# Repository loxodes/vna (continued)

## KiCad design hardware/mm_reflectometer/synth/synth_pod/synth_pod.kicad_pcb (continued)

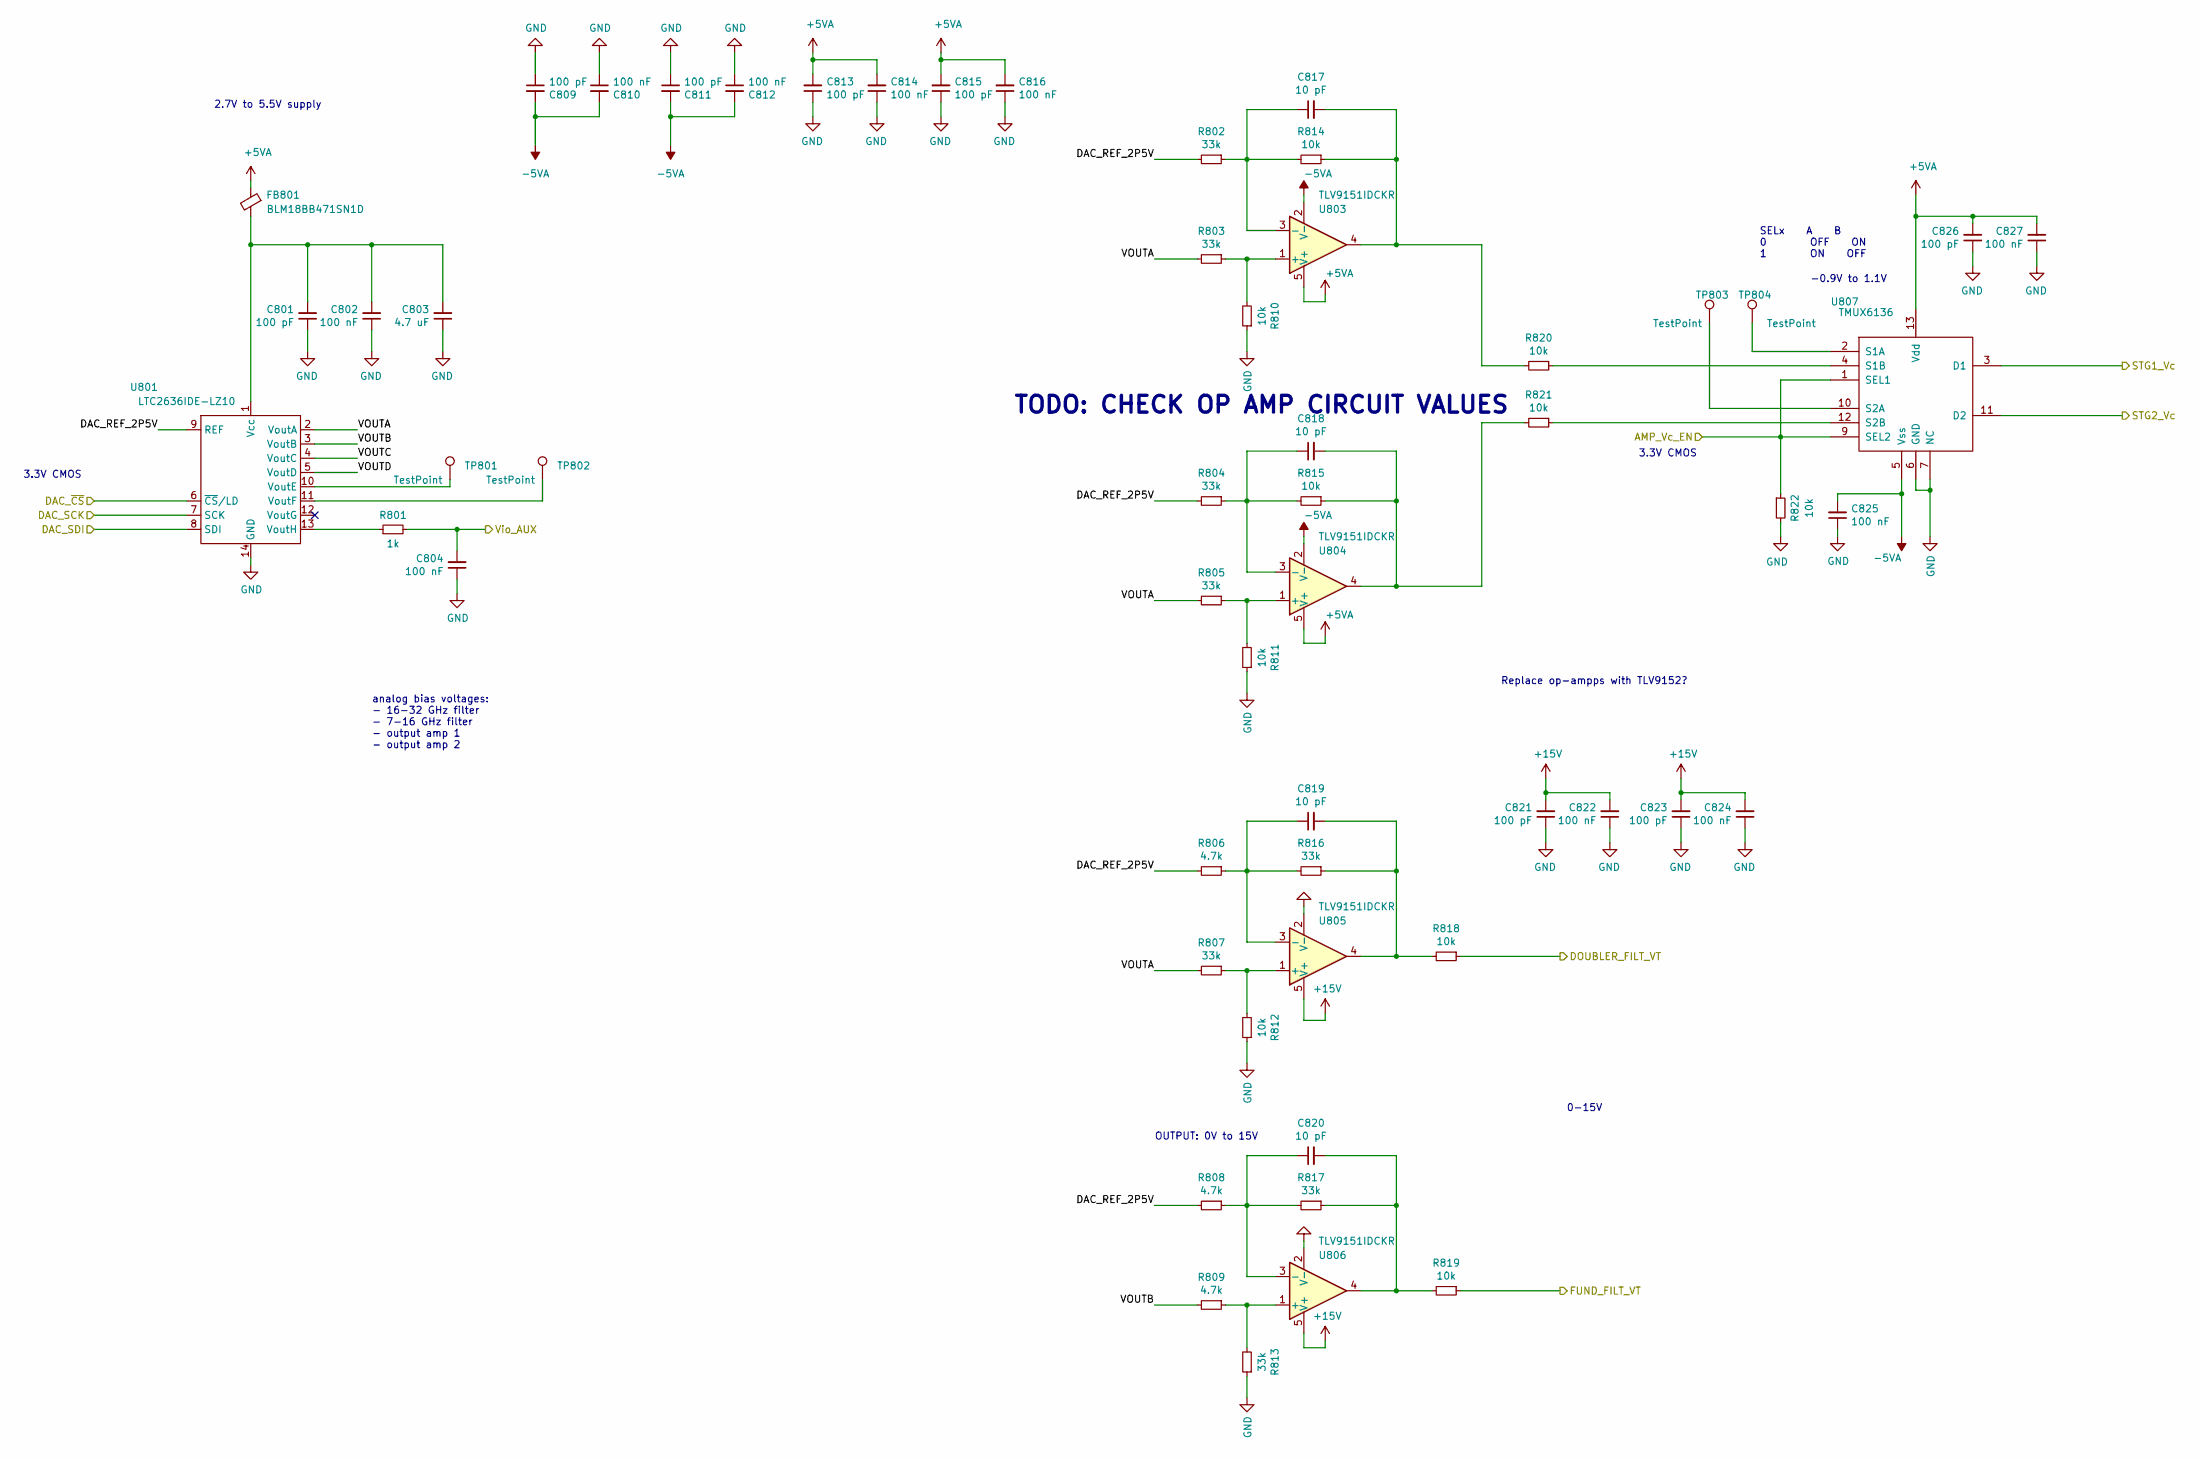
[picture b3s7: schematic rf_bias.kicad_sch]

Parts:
C801, C809, C811, C813, C815, C821, C823, C826: 100 pF; C_0402_1005Metric
C802, C804, C810, C812, C814, C816, C822, C824, C825, C827: 100 nF; C_0402_1005Metric
C803: 4.7 uF; C_0402_1005Metric
C817, C818, C819, C820: 10 pF; C_0402_1005Metric
FB801: BLM18BB471SN1D; L_0603_1608Metric
R801: 1k; R_0402_1005Metric
R802, R803, R804, R805, R807, R813, R816, R817: 33k; R_0402_1005Metric
R806, R808, R809: 4.7k; R_0402_1005Metric
R810, R811, R812, R814, R815, R818, R819, R820, R821, R822: 10k; R_0402_1005Metric
TP801, TP802, TP803, TP804: TestPoint; TestPoint_Pad_D1.5mm
U801: LTC2636IDE-LZ10; DFN-14-1EP_3x4mm_P0.5mm_EP1.7x3.3mm; mpn LTC2636-LZ10; digikey# LTC2636IDE-LZ10#PBF-ND
U803, U804, U805, U806: TLV9151IDCKR; SOT-353_SC-70-5
U807: TMUX6136; TSSOP-16_4.4x5mm_P0.65mm

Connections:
+5VA: C813.2, C814.2, C815.2, C816.2, C826.2, C827.2, FB801.1, U803.5 (V+), U804.5 (V+), U807.13 (Vdd); also elsewhere on the board
+15V: C821.2, C822.2, C823.2, C824.2, U805.5 (V+), U806.5 (V+); also elsewhere on the board
-5VA: C809.2, C810.2, C811.2, C812.2, C825.2, U803.2 (V-), U804.2 (V-), U807.5 (Vss); also elsewhere on the board
/AMP_Vc_EN: R822.1, U807.1 (SEL1), U807.9 (SEL2); also elsewhere on the board
/BIAS_DAC_SCK: U801.7 (SCK); also elsewhere on the board
/BIAS_DAC_SDI: U801.8 (SDI); also elsewhere on the board
/BIAS_DAC_~CS: U801.6 (~CS/LD); also elsewhere on the board
/DOUBLER_FILT_VT: R819.1; also elsewhere on the board
/FUND_FILT_VT: R818.1; also elsewhere on the board
/STG1_Vc: U807.3 (D1); also elsewhere on the board
/STG2_Vc: U807.11 (D2); also elsewhere on the board
/Vio_AUX: C804.2, R801.2
/rf_bias/DAC_REF_2P5V: R802.2, R804.2, R806.2, R808.2, U801.9 (REF)
/rf_bias/VOUTA: R803.2, R805.2, R807.2, U801.2 (VoutA)
/rf_bias/VOUTB: R809.2, U801.3 (VoutB)
/rf_bias/VOUTC: U801.4 (VoutC)
/rf_bias/VOUTD: U801.5 (VoutD)
GND: C801.1, C802.1, C803.1, C804.1, C809.1, C810.1, C811.1, C812.1, C813.1, C814.1, C815.1, C816.1, C821.1, C822.1, C823.1, C824.1, C825.1, C826.1, C827.1, R810.1, R811.1, R812.1, R813.1, R822.2, U801.14 (GND), U801.15 (EP), U805.2 (V-), U806.2 (V-), U807.6 (GND), U807.7 (NC), U807.8 (NC), U807.14 (NC), U807.15 (NC), U807.16 (NC); also elsewhere on the board
unnamed: C801.2, C802.2, C803.2, FB801.2, U801.1 (Vcc)
unnamed: C817.1, R802.1, R814.2, U803.3 (-)
unnamed: C817.2, R814.1, R820.2, U803.4
unnamed: C818.1, R804.1, R815.2, U804.3 (-)
unnamed: C818.2, R815.1, R821.2, U804.4
unnamed: C819.1, R806.1, R816.2, U805.3 (-)
unnamed: C819.2, R816.1, R818.2, U805.4
unnamed: C820.1, R808.1, R817.2, U806.3 (-)
unnamed: C820.2, R817.1, R819.2, U806.4
unnamed: R801.1, U801.13 (VoutH)
unnamed: R803.1, R810.2, U803.1 (+)
unnamed: R805.1, R811.2, U804.1 (+)
unnamed: R807.1, R812.2, U805.1 (+)
unnamed: R809.1, R813.2, U806.1 (+)
unnamed: R820.1, U807.4 (S1B)
unnamed: R821.1, U807.12 (S2B)
unnamed: TP801.1, U801.10 (VoutE)
unnamed: TP802.1, U801.11 (VoutF)
unnamed: TP803.1, U807.10 (S2A)
unnamed: TP804.1, U807.2 (S1A)

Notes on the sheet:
analog bias voltages: - 16-32 GHz filter - 7-16 GHz filter - output amp 1 - output amp 2
3.3V CMOS
TODO: CHECK OP AMP CIRCUIT VALUES
-0.9V to 1.1V
0-15V
2.7V to 5.5V supply
Replace op-ampps with TLV9152?
SELx A B 0 OFF ON 1 ON OFF
OUTPUT: 0V to 15V

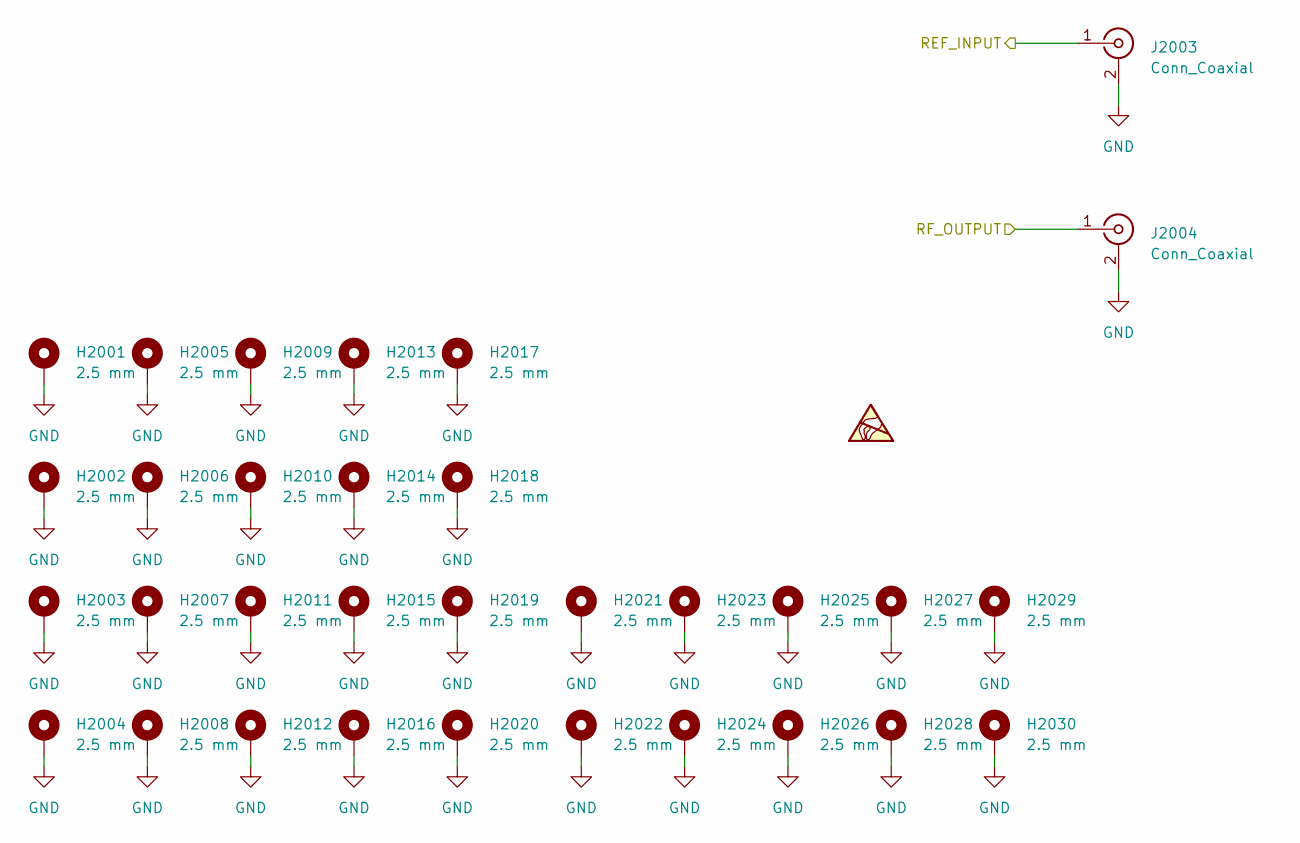
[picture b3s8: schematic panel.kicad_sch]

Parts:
H2001, H2002, H2003, H2004, H2005, H2006, H2007, H2008, H2009, H2010, H2011, H2012, H2013, H2014, H2015, H2016, H2017, H2018, H2019, H2020, H2021, H2022, H2023, H2024, H2025, H2026, H2027, H2028, H2029, H2030: 2.5 mm; MountingHole_2.5mm_Pad_Via
J2003: Conn_Coaxial; SMA_Cinch_142-0711-821_EdgeMount
J2004: Conn_Coaxial; sw_edge_oshpark_4layer

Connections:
/REF_IN: J2003.1 (In); also elsewhere on the board
/panel/RF_OUTPUT: J2004.1 (In); also elsewhere on the board
GND: H2001.1, H2002.1, H2003.1, H2004.1, H2005.1, H2006.1, H2007.1, H2008.1, H2009.1, H2010.1, H2011.1, H2012.1, H2013.1, H2014.1, H2015.1, H2016.1, H2017.1, H2018.1, H2019.1, H2020.1, H2021.1, H2022.1, H2023.1, H2024.1, H2025.1, H2026.1, H2027.1, H2028.1, H2029.1, H2030.1, J2003.2 (Ext), J2004.2 (Ext); also elsewhere on the board

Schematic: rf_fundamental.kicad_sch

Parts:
AT401: ATS2012; mpn ATS2012-xxdB-XX
C401, C405, C406, C409, C412: 10 nF; C_0402_1005Metric
C402, C407, C408, C413: 100 pF; C_0402_1005Metric
C403, C410, C411: 1 uF; C_0402_1005Metric
C404: C_Small; C_0402_1005Metric
FB401, FB402, FB403, FB404: BLM15GG471SZ1D; L_0402_1005Metric
R401, R402: R_Small; R_0402_1005Metric
U401: MAAM-011101; TDFN6; mpn MAAM-011101-TR1000; digikey# 1465-1283-1-ND
U402: ADMV8416; LFCSP-40-1EP_6x6mm_P0.5mm_EP4.7x4.7mm; mpn ADMV8416ACPZ; mouser# 584-ADMV8416ACPZ

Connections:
+3.3VA: FB401.1; also elsewhere on the board
+5VA: FB403.1; also elsewhere on the board
-5VA: FB404.1; also elsewhere on the board
/FUND_FILT_VCTL: R401.1
/FUND_FILT_VT: R402.1; also elsewhere on the board
/fundamental_b/FUND_B_IN: AT401.1; also elsewhere on the board
/fundamental_b/FUND_B_OUT: U402.26 (RFOUT); also elsewhere on the board
GND: AT401.3, C401.1, C402.1, C403.1, C405.1, C406.1, C407.1, C408.1, C409.1, C410.1, C411.1, C412.1, C413.1, U401.2 (NC), U401.4 (NC), U401.5 (NC), U401.6 (NC), U401.7 (EP), U402.1 (NC), U402.2 (NC), U402.3 (NC), U402.4 (GND), U402.6 (GND), U402.7 (NC), U402.8 (NC), U402.9 (NC), U402.10 (NC), U402.12 (GND), U402.14 (NC), U402.16 (GND), U402.17 (NC), U402.18 (GND), U402.20 (NC), U402.21 (NC), U402.22 (NC), U402.23 (NC), U402.24 (NC), U402.25 (GND), U402.27 (GND), U402.28 (NC), U402.29 (NC), U402.30 (NC), U402.31 (NC), U402.32 (NC), U402.33 (NC), U402.34 (NC), U402.35 (NC), U402.36 (NC), U402.37 (NC), U402.38 (NC), U402.39 (NC), U402.40 (NC), U402.41 (GND); also elsewhere on the board
unnamed: AT401.2, U401.3 (RFin)
unnamed: C401.2, R401.2, U402.15 (VCTL)
unnamed: C402.2, C405.2, R402.2, U402.19 (VTUNE)
unnamed: C403.2, C406.2, C408.2, FB401.2, FB402.1
unnamed: C404.1, FB402.2, U401.1 (RFout)
unnamed: C404.2, U402.5 (RFIN)
unnamed: C407.2, C409.2, C410.2, FB404.2, U402.11 (VEE)
unnamed: C411.2, C412.2, C413.2, FB403.2, U402.13 (VDD)

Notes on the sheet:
ADMV8416
0-15V ANALOG
3.3V CMOS
6.3-18 GHz

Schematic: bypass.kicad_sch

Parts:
C1001, C1002: 10 nF; C_0402_1005Metric
J1001, J1002: Conn_Coaxial; SF2921-61345
R1001, R1002: 50; R_0402_1005Metric

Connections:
/bypass/BYPASS_IN: C1002.2, R1002.1; also elsewhere on the board
/bypass/BYPASS_OUT: C1001.2, R1001.1; also elsewhere on the board
GND: J1001.2 (Ext), J1002.2 (Ext), R1001.2, R1002.2; also elsewhere on the board
unnamed: C1001.1, J1002.1 (In)
unnamed: C1002.1, J1001.1 (In)

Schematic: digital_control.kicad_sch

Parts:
J1401: SYZYGY-STD; SYZYGY_standard_pod

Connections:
+5VP: J1401.2 (+5V)
/AMP_Vc_EN: J1401.12 (S7_D3N); also elsewhere on the board
/ATT_CLK: J1401.28 (S23); also elsewhere on the board
/ATT_LE: J1401.26 (S21); also elsewhere on the board
/ATT_SERIN: J1401.30 (S25); also elsewhere on the board
/ATT_SEROUT: J1401.32 (S27); also elsewhere on the board
/BIAS_DAC_SCK: J1401.7 (S2_D0N); also elsewhere on the board
/BIAS_DAC_SDI: J1401.5 (S0_D0P); also elsewhere on the board
/BIAS_DAC_~CS: J1401.9 (S4_D2P); also elsewhere on the board
/CLK_N: J1401.36 (C2P_CLKN)
/CLK_P: J1401.34 (C2P_CLKP)
/OUT_SW_EN: J1401.20 (S15_D7N); also elsewhere on the board
/OUT_SW_V1: J1401.22 (S17); also elsewhere on the board
/OUT_SW_V2: J1401.24 (S19); also elsewhere on the board
/PLL_CE: J1401.11 (S6_D2N); also elsewhere on the board
/PLL_LD: J1401.19 (S14_D6N); also elsewhere on the board
/PLL_MUTE: J1401.18 (S13_D7P); also elsewhere on the board
/PLL_MUX: J1401.21 (S16); also elsewhere on the board
/PLL_SCK: J1401.13 (S8_D4P); also elsewhere on the board
/PLL_SDI: J1401.15 (S10_D4N); also elsewhere on the board
/PLL_SYNC: J1401.16 (S11_D5N); also elsewhere on the board
/PLL_~CS: J1401.17 (S12_D6P); also elsewhere on the board
/REFSW_SD2: J1401.14 (S9_D5P); also elsewhere on the board
/REF_EN: J1401.6 (S1_D1P); also elsewhere on the board
/REF_SEL: J1401.8 (S3_D1N); also elsewhere on the board
/RELAY_EN: J1401.10 (S5_D3P); also elsewhere on the board
/TLM_ADC_DIN: J1401.25 (S20); also elsewhere on the board
/TLM_ADC_DOUT: J1401.27 (S22); also elsewhere on the board
/TLM_ADC_SCLK: J1401.23 (S18); also elsewhere on the board
/TLM_ADC_~CS: J1401.29 (S24); also elsewhere on the board
/ctrl_power/~FPGA_RESET: J1401.31 (S26); also elsewhere on the board
/digital_control/R_GA: J1401.4 (R_GA); also elsewhere on the board
/digital_control/SCL: J1401.1 (SCL); also elsewhere on the board
/digital_control/SDA: J1401.3 (SDA); also elsewhere on the board
GND: J1401.41 (GND); also elsewhere on the board

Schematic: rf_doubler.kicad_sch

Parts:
AT501: ATS2012; mpn ATS2012-xxdB-XX
C501, C508, C515, C516: 1 uF; C_0402_1005Metric
C502, C504, C506, C510, C512, C514, C517: 10 nF; C_0402_1005Metric
C503, C507: 100 nF; C_0402_1005Metric
C505, C509, C511, C513, C518: 100 pF; C_0402_1005Metric
FB501, FB502, FB503, FB504: BLM15GG471SZ1D; L_0402_1005Metric
R501: 640; R_0402_1005Metric
R502: 4.7k; R_0402_1005Metric
R503, R504: R_Small; R_0402_1005Metric
U501: MAAM-011101; TDFN6; mpn MAAM-011101-TR1000; digikey# 1465-1283-1-ND
U502: XX1000-QT; QFN-16-1EP_3x3mm_P0.5mm_EP1.45x1.45mm; mpn XX1000-QT-0G0T
U503: ADMV8432; LFCSP-40-1EP_6x6mm_P0.5mm_EP4.7x4.7mm; mpn ADMV8432ACPZ; mouser# 584-ADMV8432ACPZ

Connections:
+3.3VA: FB501.1; also elsewhere on the board
+5VA: FB503.1; also elsewhere on the board
-5VA: C507.1, C509.1, FB504.1, R502.1, U502.6 (Vss); also elsewhere on the board
/DOUBLER_FILT_VCTL: R503.1
/DOUBLER_FILT_VT: R504.1; also elsewhere on the board
/highband/HIGHBAND_IN: AT501.1; also elsewhere on the board
/highband/HIGHBAND_OUT: U503.26 (RFOUT); also elsewhere on the board
/highband/Vg2: U502.7 (Vg2); also elsewhere on the board
/highband/active_bias/Vd: U502.13 (Vd2); also elsewhere on the board
/highband/active_bias/Vp: C506.2, C508.2, U502.15 (Vd1); also elsewhere on the board
GND: AT501.3, C501.1, C502.1, C503.2, C505.2, C506.1, C507.2, C508.1, C509.2, C510.1, C511.1, C512.1, C513.1, C514.1, C515.1, C516.1, C517.1, C518.1, R501.2, U501.2 (NC), U501.4 (NC), U501.5 (NC), U501.6 (NC), U501.7 (EP), U502.1 (NC), U502.2 (GND), U502.4 (GND), U502.8 (NC), U502.9 (GND), U502.11 (GND), U502.12 (NC), U502.14 (NC), U502.16 (NC), U502.17 (GND), U503.1 (NC), U503.2 (NC), U503.3 (NC), U503.4 (GND), U503.6 (GND), U503.7 (NC), U503.8 (NC), U503.9 (NC), U503.10 (NC), U503.12 (GND), U503.14 (NC), U503.16 (GND), U503.17 (NC), U503.18 (GND), U503.20 (NC), U503.21 (NC), U503.22 (NC), U503.23 (NC), U503.24 (NC), U503.25 (GND), U503.27 (GND), U503.28 (NC), U503.29 (NC), U503.30 (NC), U503.31 (NC), U503.32 (NC), U503.33 (NC), U503.34 (NC), U503.35 (NC), U503.36 (NC), U503.37 (NC), U503.38 (NC), U503.39 (NC), U503.40 (NC), U503.41 (GND); also elsewhere on the board
unnamed: AT501.2, U501.3 (RFin)
unnamed: C501.2, C502.2, FB501.2, FB502.1
unnamed: C503.1, C505.1, R501.1, R502.2, U502.5 (Vg1)
unnamed: C504.1, FB502.2, U501.1 (RFout)
unnamed: C504.2, U502.3 (RFin)
unnamed: C510.2, R503.2, U503.15 (VCTL)
unnamed: C511.2, C512.2, R504.2, U503.19 (VTUNE)
unnamed: C513.2, C514.2, C515.2, FB504.2, U503.11 (VEE)
unnamed: C516.2, C517.2, C518.2, FB503.2, U503.13 (VDD)
unnamed: U502.10 (RFout), U503.5 (RFIN)

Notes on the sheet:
TODO: VERIFY FOOTPRINT
3.3V CMOS
0-15V ANALOG
Sequence: GND, +5V, -5V, VCTL

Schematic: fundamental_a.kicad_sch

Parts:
C901, C904, C905: 10 nF; C_0402_1005Metric
C902, C903: 1 uF; C_0402_1005Metric
FB901, FB902: BLM15GG471SZ1D; L_0402_1005Metric
FL901: LFCN-6700; Filter_Mini-Circuits_FV1206
R901: 1.9k; R_0402_1005Metric
U901: MAAM-011206; TDFN6; mpn MAAM-011206-TR3000; mouser# 937-MAAM-011206T3

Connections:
+3.3VA: FB901.1; also elsewhere on the board
/fundamental_a/FUND_A_IN: U901.3 (RFin); also elsewhere on the board
/fundamental_a/FUND_A_OUT: FL901.3 (OUT); also elsewhere on the board
GND: C901.1, C902.1, C903.1, C905.1, FL901.2 (GND), FL901.4 (GND), U901.2 (NC), U901.4 (NC), U901.5 (NC), U901.7 (EP); also elsewhere on the board
unnamed: C901.2, C902.2, R901.1, U901.6 (Vb)
unnamed: C903.2, C905.2, FB901.2, FB902.1, R901.2
unnamed: C904.1, FB902.2, U901.1 (RFout)
unnamed: C904.2, FL901.1 (IN)

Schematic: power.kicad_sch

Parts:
C601, C603, C604, C606, C609, C611, C616, C617, C618, C622, C623, C636, C637, C639, C640: 10 uF; C_0603_1608Metric
C602, C633, C634: 1 nF; C_0402_1005Metric
C605, C626, C628, C644, C645, C646: DNI; C_0402_1005Metric
C607, C608, C614, C615, C621, C625, C627, C632: 100 nF; C_0402_1005Metric
C610, C612, C619, C620, C642, C643: 1 uF; C_0402_1005Metric
C613: 4.7 uF; C_0603_1608Metric
C624, C629, C641: 2.2 uF; C_0603_1608Metric
C630: 10 uF; C_0805_2012Metric
C635: 220 nF; C_0603_1608Metric
C638: 100 nF; C_0603_1608Metric
C647, C648: 47 uF; CP_EIA-3528-15_AVX-H
FB601, FB605, FB606: BLM18EG101TN1D; L_0603_1608Metric
FB602: BLM18BB471SN1D; L_0603_1608Metric
FB603, FB604: BLM15AG102SZ1D; L_0402_1005Metric
L601: 15 uH; L_1210_3225Metric
R601, R602, R616, R617, R618, R619, R621, R622, R625, R626: R_Small; R_0402_1005Metric
R603, R604, R607: 10k; R_0402_1005Metric
R605, R615: 0; R_0402_1005Metric
R606, R608, R620, R627, R628: DNI; R_0402_1005Metric
R609, R611: 68k; R_0402_1005Metric
R610: 39k; R_0402_1005Metric
R612: 21k; R_0402_1005Metric
R613: TBD; R_0402_1005Metric
R614: 51k; R_0402_1005Metric
R623: 2.21M; R_0402_1005Metric
R624: 0; R_0603_1608Metric
U601: ADM7171ACPZ-5.0-R7; DFN-8-1EP_3x3mm_P0.5mm_EP1.66x2.38mm
U602: LM3880MF-1AF; SOT-23-6; MPN LM3880MFX-1AF/NOPB
U603: LM27761; WSON-8-1EP_2x2mm_P0.5mm_EP0.9x1.6mm
U604, U605: TPS72301DB; SOT-23-5
U606, U607: ADM7171ACPZ-R7; DFN-8-1EP_3x3mm_P0.5mm_EP1.66x2.38mm
U608: LT3494; DFN-8-1EP_2x3mm_P0.5mm_EP0.61x2.2mm

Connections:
+3.3VA: C640.1, C643.1, C648.1, FB606.2; also elsewhere on the board
+3.3VP: C639.1, C642.1, C647.1, FB605.2; also elsewhere on the board
+4V: C621.1, C622.1, C623.1, C625.1, C627.1, FB604.1, R603.1, R604.1, U606.7 (VIN), U606.8 (VIN), U607.7 (VIN), U607.8 (VIN); also elsewhere on the board
+5V5: C601.1, C606.1, U601.7 (VIN), U601.8 (VIN), U602.1 (VCC), U603.1 (VIN), U603.6 (EN); also elsewhere on the board
+5VA: C611.1, C612.1, FB601.2; also elsewhere on the board
+15V: C630.1, R624.2; also elsewhere on the board
-3V3: C619.1, FB602.2; also elsewhere on the board
-5V35: C603.1, C604.1, C607.1, C608.1, R615.2, U604.2 (IN), U605.2 (IN)
-5VA: C620.1, FB603.2; also elsewhere on the board
/ctrl_power/PGOOD_SWITCHING: U602.3 (EN); also elsewhere on the board
/rf_power/3.3V_PLL_EN: R601.1, R603.2, R616.1, R617.1, U602.6 (FLAG1)
/rf_power/15V_BIAS_EN: R607.2, R620.1, U602.4 (FLAG3), U608.5 (~SHDN); also elsewhere on the board
/rf_power/M3V3_EN: R604.2, U602.5 (FLAG2), U604.3 (EN), U605.3 (EN)
GND: C601.2, C602.2, C603.2, C604.2, C606.2, C607.2, C608.2, C609.2, C611.2, C612.2, C613.2, C614.2, C615.2, C616.2, C617.2, C618.2, C619.2, C620.2, C621.2, C622.2, C623.2, C624.2, C625.2, C627.2, C629.2, C630.2, C632.2, C633.2, C634.2, C635.2, C636.2, C637.2, C638.2, C639.2, C640.2, C641.2, C642.2, C643.2, C647.2, C648.2, R602.2, R606.1, R610.2, R612.2, R614.2, R618.2, R619.2, R620.2, R622.1, R626.1, U601.6 (GND), U601.9 (GND), U602.2 (GND), U603.2 (GND), U603.9 (PAD), U604.1 (GND), U605.1 (GND), U606.6 (GND), U606.9 (GND), U607.6 (GND), U607.9 (GND), U608.2 (GND), U608.9 (GND); also elsewhere on the board
unnamed: C602.1, U601.4 (SS)
unnamed: C605.1, C609.1, FB601.1, R605.2, U601.1 (VOUT), U601.2 (VOUT)
unnamed: C605.2, R608.2
unnamed: C610.1, U603.8 (C+)
unnamed: C610.2, U603.7 (C-)
unnamed: C613.1, U603.3 (CPOUT)
unnamed: C614.1, C617.1, C644.1, FB602.1, R609.1, U604.5 (OUT)
unnamed: C615.1, C618.1, C645.1, FB603.1, R611.1, U605.5 (OUT)
unnamed: C616.1, C646.1, R613.1, R615.1, U603.4 (VOUT)
unnamed: C624.1, C629.1, C632.1, FB604.2, L601.1, U608.3 (Vcc)
unnamed: C626.1, C636.1, FB605.1, R621.2, U606.1 (VOUT), U606.2 (VOUT)
unnamed: C626.2, R627.2
unnamed: C628.1, C637.1, FB606.1, R625.2, U607.1 (VOUT), U607.2 (VOUT)
unnamed: C628.2, R628.2
unnamed: C633.1, U606.4 (SS)
unnamed: C634.1, U607.4 (SS)
unnamed: C635.1, U608.8 (CAP)
unnamed: C638.1, C641.1, R623.1, R624.1, U608.7 (Vout)
unnamed: C644.2, R609.2, R610.1, U604.4 (FB)
unnamed: C645.2, R611.2, R612.1, U605.4 (FB)
unnamed: C646.2, R613.2, R614.1, U603.5 (VFB)
unnamed: L601.2, U608.1 (SW)
unnamed: R601.2, R602.1, U601.5 (EN)
unnamed: R605.1, R606.2, R608.1, U601.3 (SENSE)
unnamed: R616.2, R618.1, U606.5 (EN)
unnamed: R617.2, R619.1, U607.5 (EN)
unnamed: R621.1, R622.2, R627.1, U606.3 (SENSE)
unnamed: R623.2, U608.6 (FB)
unnamed: R625.1, R626.2, R628.1, U607.3 (SENSE)

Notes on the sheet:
CHANGE TO ADM7172ACPZ-R7
200 mA
50 mA
650 mA
CHECK RESISTOR VALUES
750 mA
100 mA
Sequence: 1) +5V, +3.3V 2) -5V, -3.3V 3) +15V, Digital

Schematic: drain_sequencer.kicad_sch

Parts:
D1101: MM5Z3V3T1G; D_SOD-523
Q1101: BC848W; SOT-323_SC-70
Q1102: IRLML6401; SOT-23
R1101, R1103, R1104: 10k; R_0402_1005Metric
R1102: 0; R_0402_1005Metric

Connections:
+5VA: Q1102.2 (S), R1104.2; also elsewhere on the board
-5VA: D1101.2 (A); also elsewhere on the board
/highband/active_bias/Vp: R1102.2; also elsewhere on the board
GND: R1101.2; also elsewhere on the board
unnamed: D1101.1 (K), Q1101.2 (E)
unnamed: Q1101.1 (B), R1101.1
unnamed: Q1101.3 (C), R1103.1
unnamed: Q1102.1 (G), R1103.2, R1104.1
unnamed: Q1102.3 (D), R1102.1

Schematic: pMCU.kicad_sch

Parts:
C1601: 100 nF; C_0402_1005Metric
C1602: 1 uF; C_0402_1005Metric
J1601: TC2050-IDC-NL; TAG-CONNECT_TC2050-IDC-NL; PARTREV A
R1601: 10k; R_0402_1005Metric
U1601: ATtiny24A-MM; QFN-20-1EP_3x3mm_P0.45mm_EP1.6x1.6mm

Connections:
/digital_control/R_GA: R1601.2, U1601.5 (AREF/PA0); also elsewhere on the board
/digital_control/SCL: J1601.7, U1601.1 (PA4); also elsewhere on the board
/digital_control/SDA: J1601.1, U1601.16 (PA6); also elsewhere on the board
/digital_control/pMCU/pMCU_MISO: J1601.9, U1601.20 (PA5)
/digital_control/pMCU/pMCU_~RST: J1601.5, U1601.13 (~RESET/PB3)
GND: C1601.2, C1602.2, J1601.4, J1601.6, J1601.8, J1601.10, U1601.8 (GND), U1601.21 (GND); also elsewhere on the board

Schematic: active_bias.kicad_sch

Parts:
C1201, C1202, C1207, C1208: 100 pF; C_0402_1005Metric
C1203, C1206, C1209, C1210: 100 nF; C_0402_1005Metric
C1204: 1 nH; C_0402_1005Metric
C1205: 4.7 uF; C_0603_1608Metric
D1201, D1202, D1203: BAS516; D_SOD-523
R1201: 15k; R_0402_1005Metric
R1202: DNI; R_0402_1005Metric
R1203: 0.5; R_0603_1608Metric
R1204: 0; R_0402_1005Metric
R1205, R1206, R1207, R1208: 1k; R_0402_1005Metric
R1209: 100k; R_0402_1005Metric
U1201: TLV9151IDCKR; SOT-353_SC-70-5

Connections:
+5VA: C1206.1, C1207.1, R1208.1, U1201.5 (V+); also elsewhere on the board
-5VA: C1208.1, C1209.1, R1201.1, U1201.2 (V-); also elsewhere on the board
/highband/Vg2: C1202.1, C1204.1, R1202.2, R1204.2; also elsewhere on the board
/highband/active_bias/Vd: C1201.1, C1203.1, C1205.1, R1203.2, R1206.1; also elsewhere on the board
/highband/active_bias/Vp: R1203.1; also elsewhere on the board
GND: C1201.2, C1202.2, C1203.2, C1204.2, C1205.2, C1206.2, C1207.2, C1208.2, C1209.2, C1210.2, D1201.1 (K), D1203.2 (A), R1202.1, R1209.2; also elsewhere on the board
unnamed: C1210.1, R1207.1, R1208.2, R1209.1
unnamed: D1201.2 (A), D1202.1 (K), R1201.2, R1204.1, R1205.1
unnamed: D1202.2 (A), D1203.1 (K)
unnamed: R1205.2, U1201.4
unnamed: R1206.2, U1201.1 (+)
unnamed: R1207.2, U1201.3 (-)

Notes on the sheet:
TODO: CALCULATE RESISTORS FOR 4.8V, ID = 140 mA

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
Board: 8 copper layers, 505 parts (0 on the bottom side), 291 nets, no tracks yet.

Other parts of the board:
D1901: MM5Z3V3T1G; D_SOD-523
Q1901: BC848W; SOT-323_SC-70
Q1902: IRLML6401; SOT-23
R1901, R1903, R1904: 10k; R_0402_1005Metric
R1902: 0; R_0402_1005Metric

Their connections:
+5VA: Q1902.2 (S), R1904.2; also elsewhere on the board
-5VA: D1901.2 (A); also elsewhere on the board
/rf_output/drain_sequencer1/Vd_sequenced: R1902.2; also elsewhere on the board
GND: R1901.2; also elsewhere on the board
unnamed: D1901.1 (K), Q1901.2 (E)
unnamed: Q1901.1 (B), R1901.1
unnamed: Q1901.3 (C), R1903.1
unnamed: Q1902.1 (G), R1903.2, R1904.1
unnamed: Q1902.3 (D), R1902.1

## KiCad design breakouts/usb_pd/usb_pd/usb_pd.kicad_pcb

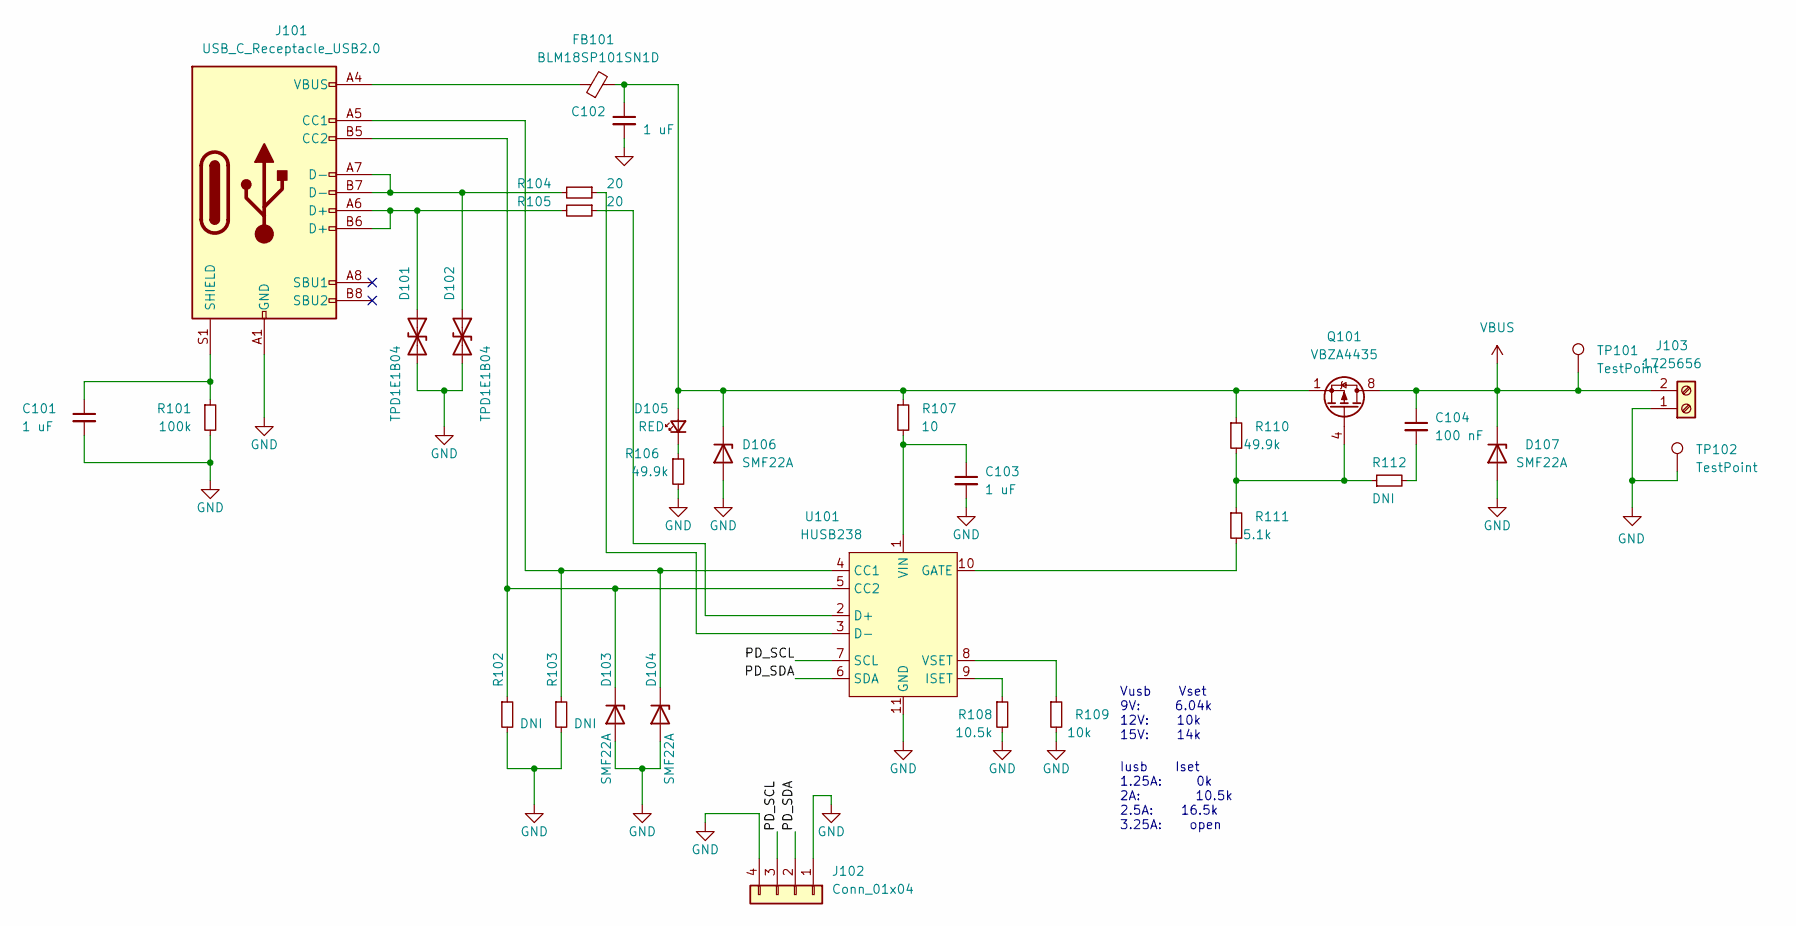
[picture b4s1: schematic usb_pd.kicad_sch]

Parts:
C101, C102, C103: 1 uF; C_0402_1005Metric
C104: 100 nF; C_0402_1005Metric
D101, D102: TPD1E1B04; D_0402_1005Metric
D103, D104, D106, D107: SMF22A; D_SOD-123F
D105: RED; LED_0603_1608Metric
FB101: BLM18SP101SN1D; L_0603_1608Metric
J101: USB_C_Receptacle_USB2.0; USB_C_Receptacle_HRO_TYPE-C-31-M-12
J102: Conn_01x04; PinHeader_1x04_P2.54mm_Vertical
J103: 1725656; TerminalBlock_Phoenix_MPT-0,5-2-2.54_1x02_P2.54mm_Horizontal
Q101: VBZA4435; SOIC-8_3.9x4.9mm_P1.27mm
R101: 100k; R_0402_1005Metric
R102, R103, R112: DNI; R_0402_1005Metric
R104, R105: 20; R_0402_1005Metric
R106, R110: 49.9k; R_0402_1005Metric
R107: 10; R_0402_1005Metric
R108: 10.5k; R_0402_1005Metric
R109: 10k; R_0402_1005Metric
R111: 5.1k; R_0402_1005Metric
TP101, TP102: TestPoint; TestPoint_Keystone_5015_Micro-Minature
U101: HUSB238; DFN-10-1EP_3x3mm_P0.5mm_EP1.65x2.38mm

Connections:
/PD_SCL: J102.3, U101.7 (SCL)
/PD_SDA: J102.2, U101.6 (SDA)
GND: C101.2, C102.2, C103.2, D101.2 (A2), D102.2 (A2), D103.2 (A), D104.2 (A), D106.2 (A), D107.2 (A), J101.A1 (GND), J101.A12 (GND), J101.B1 (GND), J101.B12 (GND), J102.1, J102.4, J103.1, R101.2, R102.2, R103.2, R106.2, R108.2, R109.2, TP102.1, U101.11 (GND)
unnamed: C101.1, J101.S1 (SHIELD), R101.1
unnamed: C102.1, D105.2 (A), D106.1 (K), FB101.2, Q101.1 (S), Q101.2 (S), Q101.3 (S), R107.1, R110.1
unnamed: C103.1, R107.2, U101.1 (VIN)
unnamed: C104.2, R112.2
unnamed: D101.1 (A1), J101.A6 (D+), J101.B6 (D+), R105.2
unnamed: D102.1 (A1), J101.A7 (D-), J101.B7 (D-), R104.2
unnamed: D103.1 (K), J101.B5 (CC2), R102.1, U101.5 (CC2)
unnamed: D104.1 (K), J101.A5 (CC1), R103.1, U101.4 (CC1)
unnamed: D105.1 (K), R106.1
unnamed: FB101.1, J101.A4 (VBUS), J101.A9 (VBUS), J101.B4 (VBUS), J101.B9 (VBUS)
unnamed: Q101.4 (G), R110.2, R111.1, R112.1
unnamed: R104.1, U101.3 (D-)
unnamed: R105.1, U101.2 (D+)
unnamed: R108.1, U101.9 (ISET)
unnamed: R109.1, U101.8 (VSET)
unnamed: R111.2, U101.10 (GATE)
VBUS: C104.1, D107.1 (K), J103.2, Q101.5 (D), Q101.6 (D), Q101.7 (D), Q101.8 (D), TP101.1

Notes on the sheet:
Vusb Vset 9V: 6.04k 12V: 10k 15V: 14k
Iusb Iset 1.25A: 0k 2A: 10.5k 2.5A: 16.5k 3.25A: open

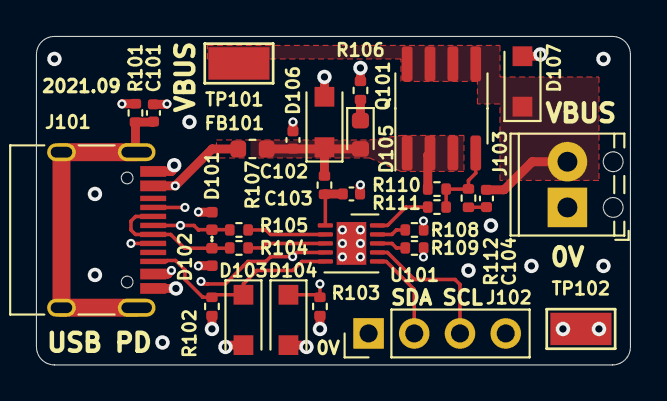
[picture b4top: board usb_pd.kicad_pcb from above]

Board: 4 copper layers, 33.0 x 18.2 mm, 31 parts (0 on the bottom side), 20 nets.
